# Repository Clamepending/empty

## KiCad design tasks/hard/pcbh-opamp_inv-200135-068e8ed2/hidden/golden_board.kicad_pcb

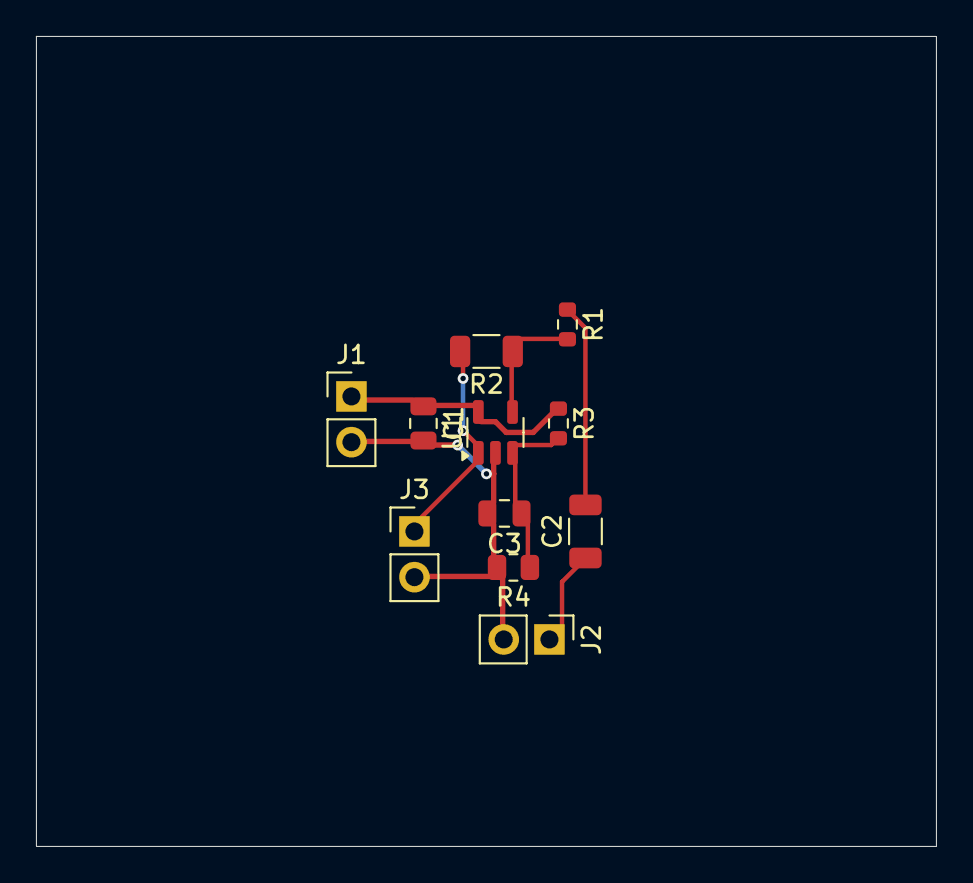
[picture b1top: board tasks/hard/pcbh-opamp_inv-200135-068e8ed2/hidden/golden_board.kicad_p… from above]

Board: 2 copper layers, 50.0 x 45.0 mm, 11 parts (0 on the bottom side), 7 nets.

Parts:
C1: 100n; C_0805_2012Metric
C2: 1u; C_1206_3216Metric
C3: 10u; C_0805_2012Metric
J1, J2, J3: PinHeader_1x02_P2.54mm_Vertical
R1: 2.74k; R_0603_1608Metric
R2: 9.09k; R_1206_3216Metric
R3: 75k; R_0603_1608Metric
R4: 75k; R_0805_2012Metric
U1: SOT-23-5

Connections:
GND: C1.2, C3.2, J1.2, J2.2, J3.2, R4.2, U1.2
IN: C2.1, J2.1
IN_AC: C2.2, R1.1
OUT: J3.1, R2.2, U1.1
SUM: R1.2, R2.1, U1.4
VCC: C1.1, J1.1, R3.1, U1.5
VMID: C3.1, R3.2, R4.1, U1.3

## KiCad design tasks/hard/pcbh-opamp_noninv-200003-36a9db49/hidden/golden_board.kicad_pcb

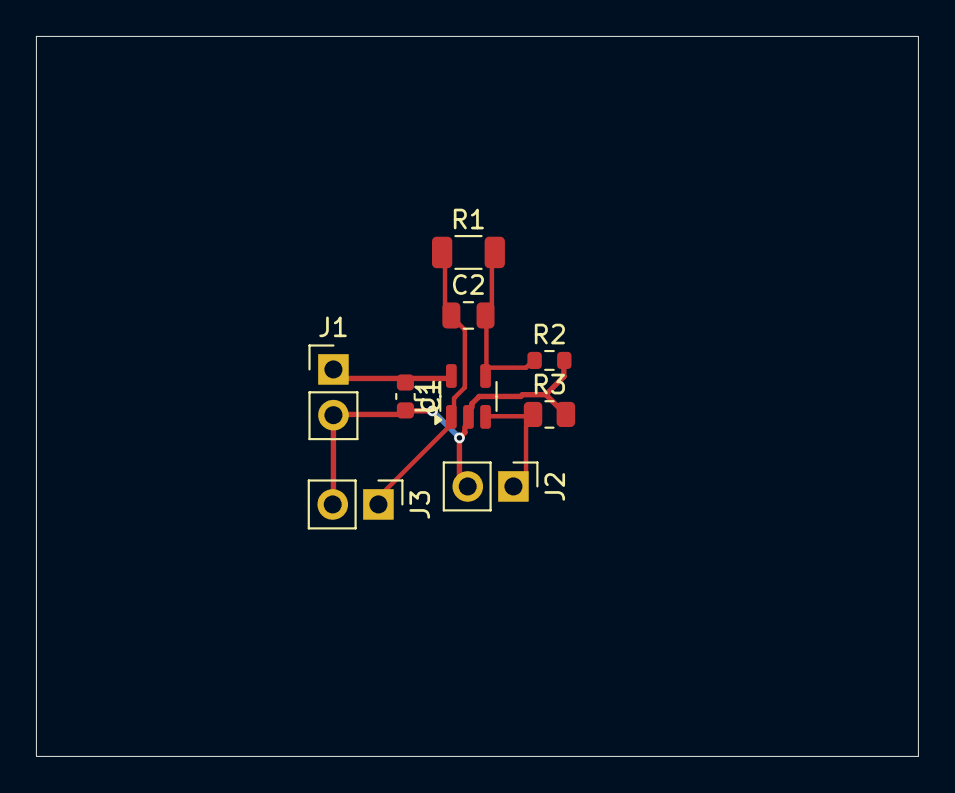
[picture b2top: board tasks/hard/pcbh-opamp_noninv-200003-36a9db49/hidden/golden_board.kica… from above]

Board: 2 copper layers, 49.0 x 40.0 mm, 9 parts (0 on the bottom side), 5 nets.

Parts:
C1: 100n; C_0603_1608Metric
C2: 220p; C_0805_2012Metric
J1, J2, J3: PinHeader_1x02_P2.54mm_Vertical
R1: 113k; R_1206_3216Metric
R2: 8.06k; R_0603_1608Metric
R3: 220k; R_0805_2012Metric
U1: SOT-23-5

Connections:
FB: C2.2, R1.2, R2.1, U1.4
GND: C1.2, J1.2, J2.2, J3.2, R2.2, R3.2, U1.2
IN: J2.1, R3.1, U1.3
OUT: C2.1, J3.1, R1.1, U1.1
VCC: C1.1, J1.1, U1.5

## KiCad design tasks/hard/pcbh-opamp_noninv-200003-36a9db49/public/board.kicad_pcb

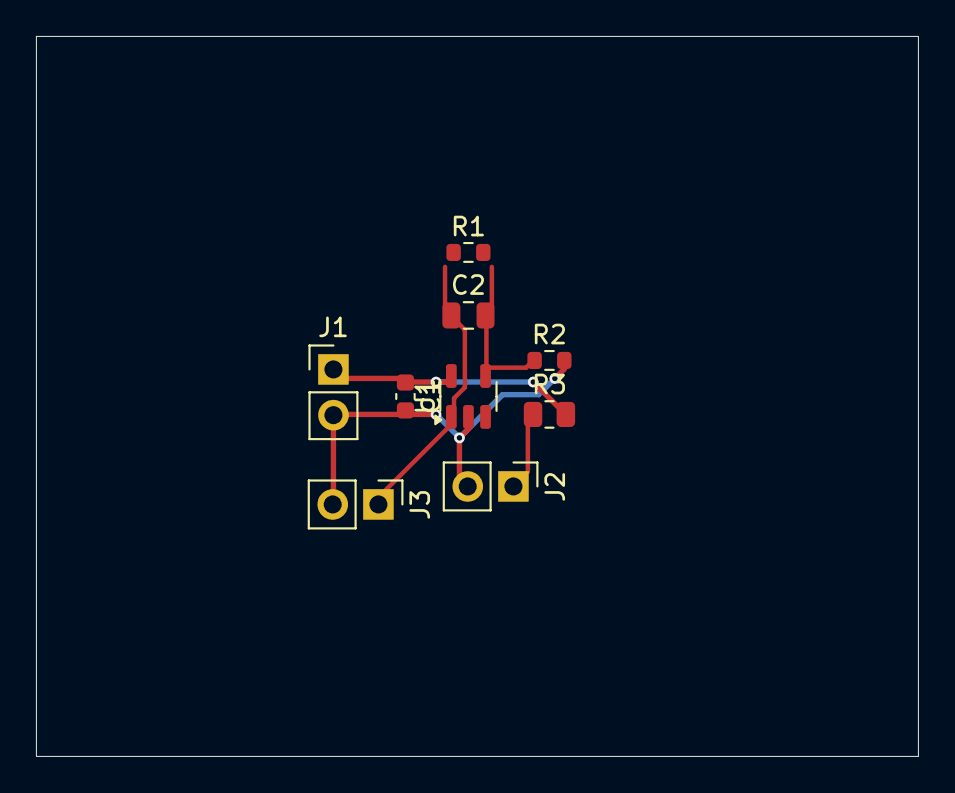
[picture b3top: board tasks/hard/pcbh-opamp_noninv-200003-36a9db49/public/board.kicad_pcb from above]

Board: 2 copper layers, 49.0 x 40.0 mm, 9 parts (0 on the bottom side), 5 nets.

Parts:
C1: 100n; C_0603_1608Metric
C2: 150p; C_0805_2012Metric
J1, J2, J3: PinHeader_1x02_P2.54mm_Vertical
R1: 113k; R_0603_1608Metric
R2: 8.06k; R_0603_1608Metric
R3: 220k; R_0805_2012Metric
U1: SOT-23-5

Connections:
FB: C2.2, R1.2, R2.1, U1.4
GND: C1.2, J1.2, J2.2, J3.2, R2.2, U1.2
IN: J2.1, R3.1
OUT: C2.1, J3.1, R1.1, U1.1
VCC: C1.1, J1.1, R3.2, U1.5

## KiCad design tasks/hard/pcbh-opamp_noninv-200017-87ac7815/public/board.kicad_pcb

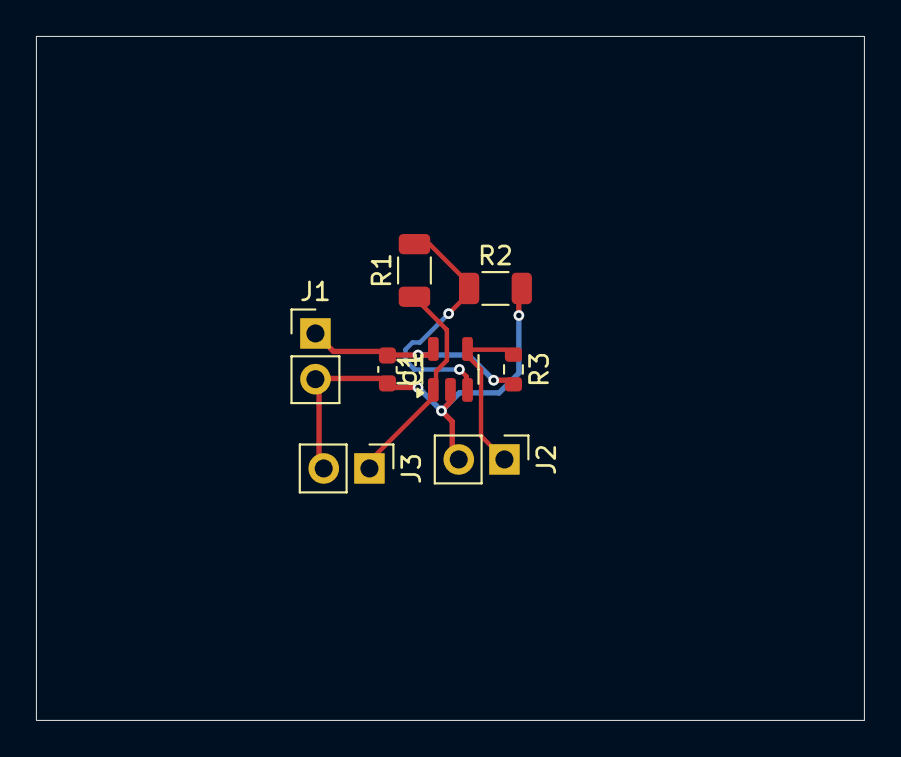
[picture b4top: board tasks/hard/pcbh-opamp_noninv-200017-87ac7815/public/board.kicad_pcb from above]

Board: 2 copper layers, 46.0 x 38.0 mm, 8 parts (0 on the bottom side), 5 nets.

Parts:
C1: 100n; C_0603_1608Metric
J1, J2, J3: PinHeader_1x02_P2.54mm_Vertical
R1, R2: 3.09k; R_1206_3216Metric
R3: 220k; R_0603_1608Metric
U1: SOT-23-5

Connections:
FB: R1.2, R2.1, U1.3
GND: C1.2, J1.2, J2.2, J3.2, R2.2, U1.2
IN: J2.1, R3.1, U1.4
OUT: J3.1, R1.1, U1.1
VCC: C1.1, J1.1, R3.2, U1.5
